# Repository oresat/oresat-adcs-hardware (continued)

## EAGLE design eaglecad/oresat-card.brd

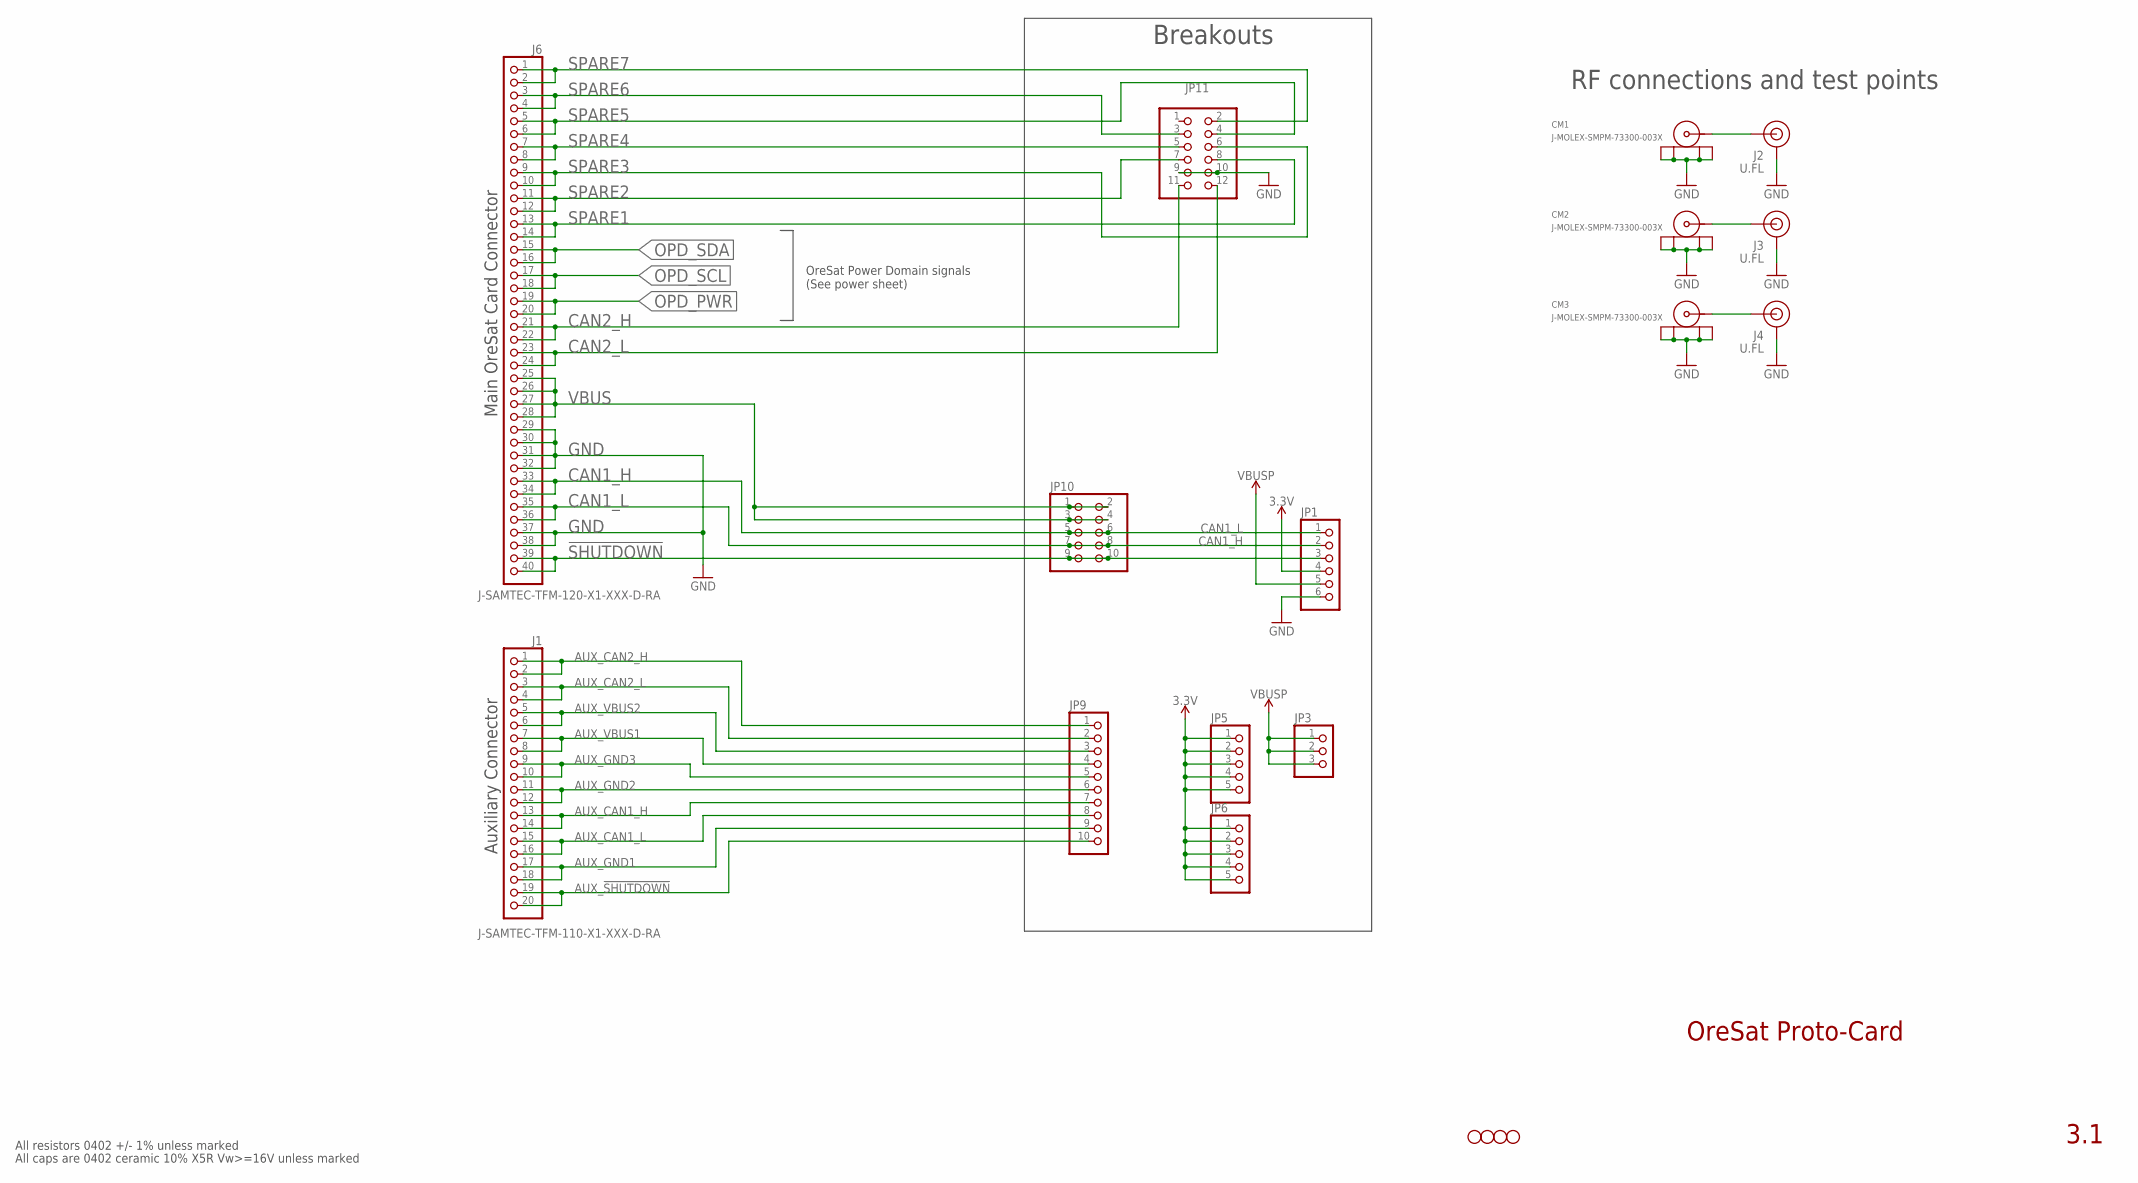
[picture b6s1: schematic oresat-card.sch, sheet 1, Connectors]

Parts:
CM1, CM2, CM3: J-MOLEX-SMPM-73300-003X; J-MOLEX-SMPM-073300-003X; MPN 73300-0020
H1, H2, H3, H4: STAND-OFFTIGHT; STAND-OFF-TIGHT
J1: J-SAMTEC-TFM-110-X1-XXX-D-RA; MPN TFM-110-01-L-D-RA
J2, J3, J4: U.FL
J6: J-SAMTEC-TFM-120-X1-XXX-D-RA; MPN TFM-120-01-L-D-RA
JP1: PINHD-1X6; 1X06
JP3: PINHD-1X3; 1X03
JP5, JP6: PINHD-1X5; 1X05
JP9: PINHD-1X10; 1X10
JP10: PINHD-2X5; 2X05
JP11: PINHD-2X6; 2X06

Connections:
3.3V: JP1.4, JP5.1, JP5.2, JP5.3, JP5.4, JP5.5, JP6.1, JP6.2, JP6.3, JP6.4, JP6.5
!SHUTDOWN: J6.39, J6.40, JP1.3, JP10.9, JP10.10
AUX_!SHUTDOWN: J1.19, J1.20, JP9.10
AUX_CAN1_H: J1.13, J1.14, JP9.7
AUX_CAN1_L: J1.15, J1.16, JP9.8
AUX_CAN2_H: J1.1, J1.2, JP9.1
AUX_CAN2_L: J1.3, J1.4, JP9.2
AUX_GND1: J1.17, J1.18, JP9.9
AUX_GND2: J1.11, J1.12, JP9.6
AUX_GND3: J1.9, J1.10, JP9.5
AUX_VBUS1: J1.7, J1.8, JP9.4
AUX_VBUS2: J1.5, J1.6, JP9.3
CAN1_H: J6.33, J6.34, JP1.1, JP10.5, JP10.6
CAN1_L: J6.35, J6.36, JP1.2, JP10.7, JP10.8
CAN2_H: J6.21, J6.22, JP11.11
CAN2_L: J6.23, J6.24, JP11.12
GND: CM1.P$1 (SHIELD3), CM1.P$2 (SHIELD2), CM1.P$3 (SHIELD1), CM1.P$4 (SHIELD), CM2.P$1 (SHIELD3), CM2.P$2 (SHIELD2), CM2.P$3 (SHIELD1), CM2.P$4 (SHIELD), CM3.P$1 (SHIELD3), CM3.P$2 (SHIELD2), CM3.P$3 (SHIELD1), CM3.P$4 (SHIELD), J2.1 (GND), J2.2 (GND), J3.1 (GND), J3.2 (GND), J4.1 (GND), J4.2 (GND), J6.29, J6.30, J6.31, J6.32, J6.37, J6.38, JP1.6, JP11.9, JP11.10; also elsewhere on the board
unnamed: CM3.RF (CENTER), J4.FEED (SIGNAL)
OPD_PWR: J6.19, J6.20; also elsewhere on the board
OPD_SCL: J6.17, J6.18; also elsewhere on the board
OPD_SDA: J6.15, J6.16; also elsewhere on the board
RF1: CM1.RF (CENTER), J2.FEED (SIGNAL)
RF2: CM2.RF (CENTER), J3.FEED (SIGNAL)
SPARE1: J6.13, J6.14, JP11.8
SPARE2: J6.11, J6.12, JP11.7
SPARE3: J6.9, J6.10, JP11.6
SPARE4: J6.7, J6.8, JP11.5
SPARE5: J6.5, J6.6, JP11.4
SPARE6: J6.3, J6.4, JP11.3
SPARE7: J6.1, J6.2, JP11.2
VBUS: J6.25, J6.26, J6.27, J6.28, JP10.1, JP10.2, JP10.3, JP10.4; also elsewhere on the board
VBUSP: JP1.5, JP3.1, JP3.2, JP3.3; also elsewhere on the board

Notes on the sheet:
OreSat Proto-Card
3.1
All resistors 0402 +/- 1% unless marked
All caps are 0402 ceramic 10% X5R Vw>=16V unless marked
Auxiliary Connector
Main OreSat Card Connector
RF connections and test points
Breakouts
OreSat Power Domain signals (See power sheet)

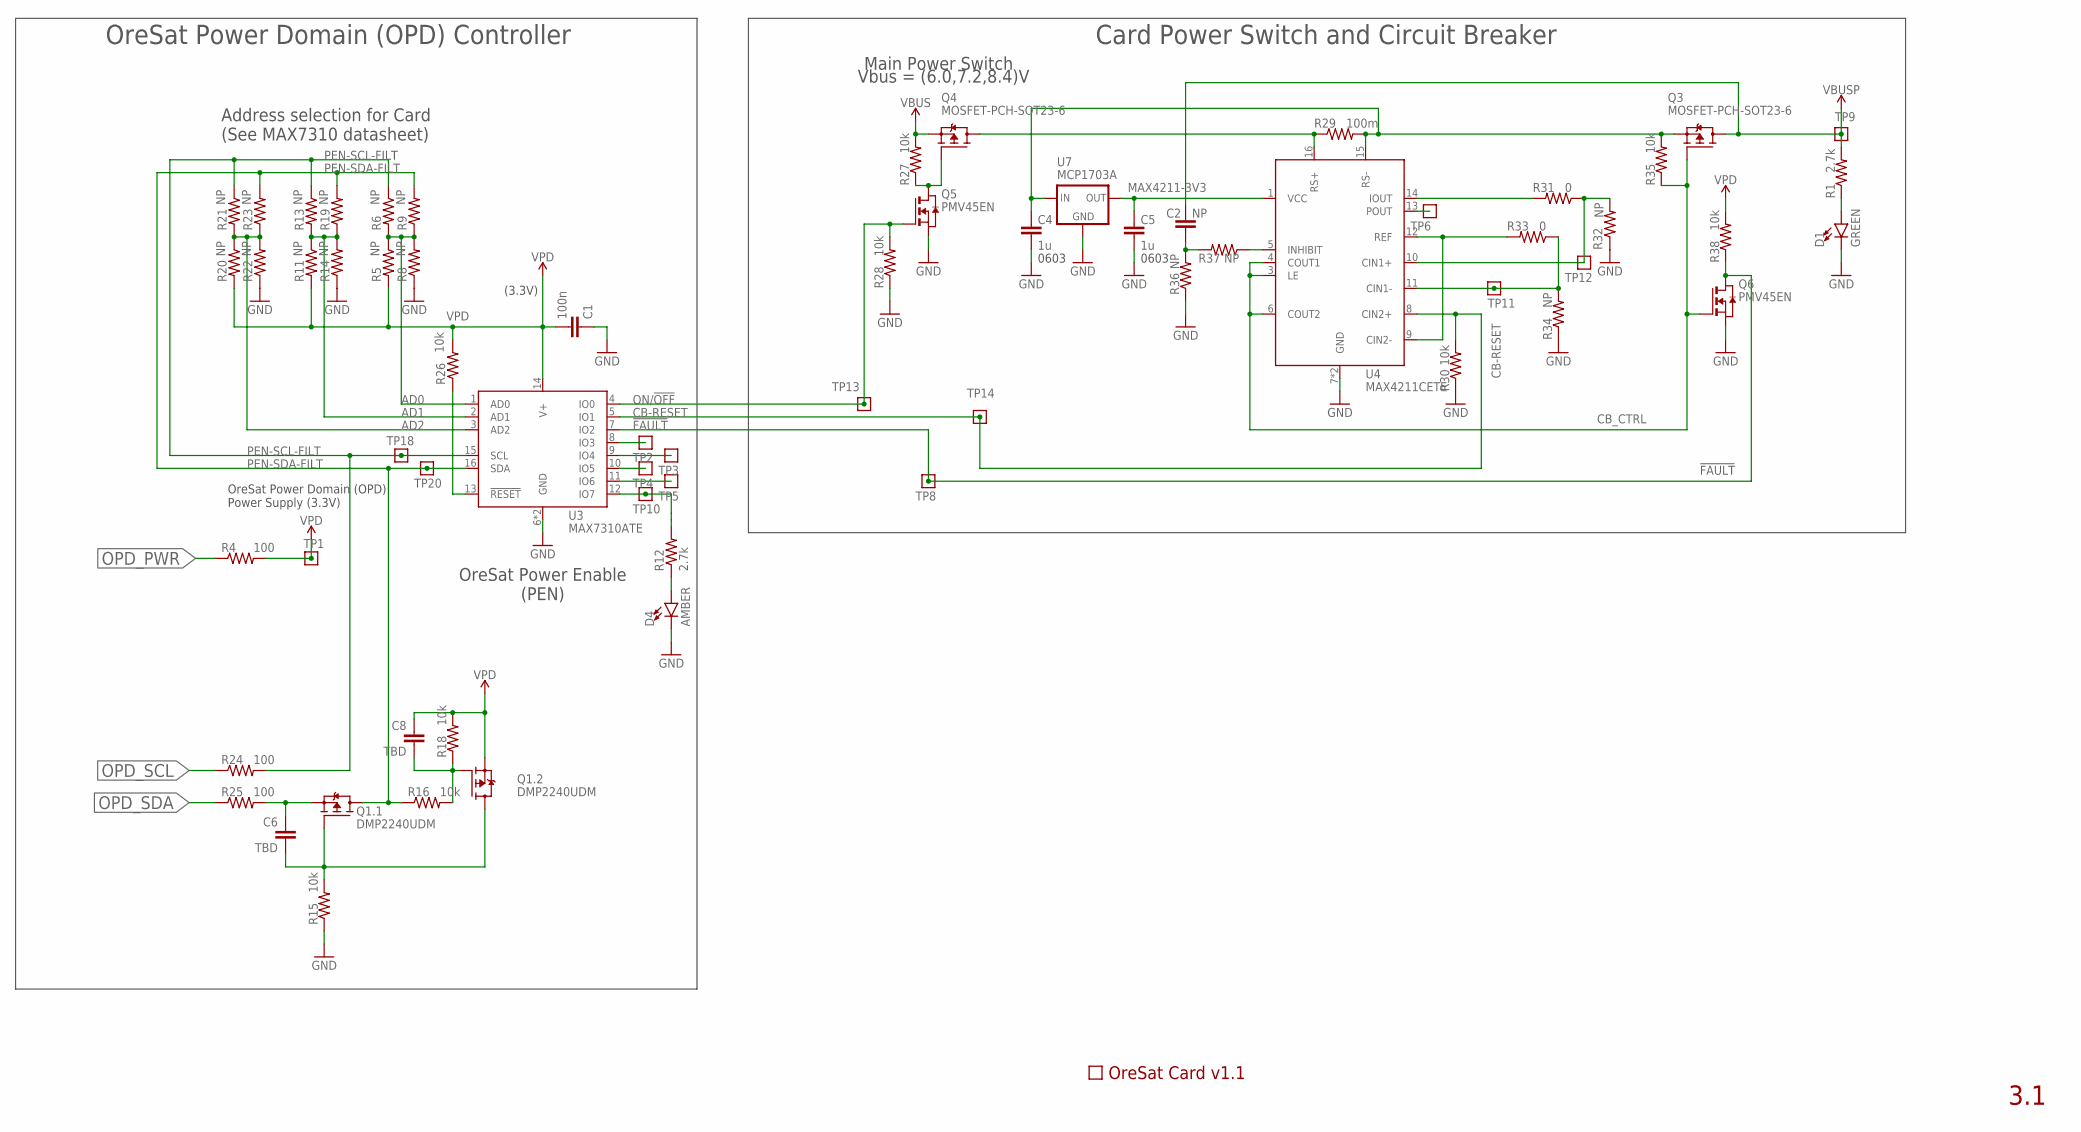
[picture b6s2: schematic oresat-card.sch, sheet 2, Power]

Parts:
C1: 100n; .0402-B-NOSILK; MPN CL05B104KO5NNNC
C2: NP; .0402-B-NOSILK; MPN CL05B104KO5NNNC
C4, C5: 1u; .0603-B-NOSILK; MPN CL05B104KO5NNNC
C6, C8: TBD; .0402-B-NOSILK; MPN CL05B104KO5NNNC
D1: GREEN; LED-0603
D4: AMBER; LED-0603
Q1: DMP2240UDM; SOT23-6; MPN DMP2240UDM
Q3, Q4: MOSFET-PCH-SOT23-6; SOT23-6; MPN DMP3050LVT-7
Q5, Q6: PMV45EN; SOT23
R1, R12: 2.7k; .0402-B-NOSILK; MPN RC1005F6653CS
R4, R24, R25: 100; .0402-B-NOSILK; MPN RC1005F6653CS
R5, R6, R8, R9, R11, R13, R14, R19, R20, R21, R22, R23, R32, R34, R36, R37: NP; .0402-B-NOSILK; MPN RC1005F6653CS
R15, R16, R18, R26, R27, R28, R30, R35, R38: 10k; .0402-B-NOSILK; MPN RC1005F6653CS
R29: 100m; R1206
R31, R33: 0; .0402-B-NOSILK; MPN RC1005F6653CS
TP1, TP2, TP3, TP4, TP5, TP6, TP8, TP9, TP10, TP11, TP12, TP13, TP14, TP18, TP20: TEST-POINT; 2MM-TEST-POINT
U3: MAX7310ATE; QFN65P400X400X80-17T210; MPN MAX7310ATE
U4: MAX4211CETE; QFN65P400X400X80-17T210; MPN MAX4211CETE
U7: MCP1703A; SOT23; MPN MCP1703AT-3302E/CB
U$1: ORESAT-CARD-V1.1-3XRF

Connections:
!FAULT: Q6.3 (D), R38.1, TP8.1, U3.7 (IO2)
AD0: R5.1, R6.2, R8.2, R9.1, U3.1 (AD0)
AD1: R11.1, R13.2, R14.2, R19.1, U3.2 (AD1)
AD2: R20.1, R21.2, R22.2, R23.1, U3.3 (AD2)
CB-RESET: R30.2, TP14.1, U3.5 (IO1), U4.8 (CIN2+)
CB_CTRL: Q3.3 (G), Q6.1 (G), R35.1, U4.3 (LE), U4.4 (COUT1), U4.6 (COUT2)
GND: C1.1, C4.2, C5.2, D1.C, D4.C, Q5.2 (S), Q6.2 (S), R8.1, R14.1, R15.1, R22.1, R28.1, R30.1, R32.1, R34.1, R36.1, U3.6 (GND), U3.EPAD (GND), U4.7 (GND), U4.EPAD (GND), U7.1 (GND); also elsewhere on the board
MAX4211-3V3: C5.1, U4.1 (VCC), U7.2 (OUT)
unnamed: D1.A, R1.1
unnamed: C4.1, Q3.4 (S), R29.2, R35.2, U4.15 (RS-), U7.3 (IN)
unnamed: TP2.1, U3.8 (IO3)
unnamed: TP3.1, U3.9 (IO4)
unnamed: TP4.1, U3.10 (IO5)
unnamed: TP5.1, U3.11 (IO6)
unnamed: R12.2, TP10.1, U3.12 (IO7)
unnamed: D4.A, R12.1
unnamed: C6.1, Q1.5 (S), R25.2
unnamed: C6.2, Q1.1 (G), Q1.4 (D), R15.2
unnamed: C8.2, Q1.3 (G), R16.2, R18.1
unnamed: R26.1, U3.13 (!RESET)
unnamed: Q4.3 (G), Q5.3 (D), R27.1
unnamed: Q4.1 (D), Q4.2 (D), Q4.5 (D), Q4.6 (D), R29.1, U4.16 (RS+)
unnamed: R31.1, R32.2, TP12.1, U4.10 (CIN1+)
unnamed: R33.1, R34.2, TP11.1, U4.11 (CIN1-)
unnamed: R31.2, U4.14 (IOUT)
unnamed: R33.2, U4.9 (CIN2-), U4.12 (REF)
unnamed: TP6.1, U4.13 (POUT)
unnamed: C2.1, R36.2, R37.2
unnamed: R37.1, U4.5 (INHIBIT)
ON/!OFF: Q5.1 (G), R28.2, TP13.1, U3.4 (IO0)
OPD_PWR: R4.1; also elsewhere on the board
OPD_SCL: R24.1; also elsewhere on the board
OPD_SDA: R25.1; also elsewhere on the board
PEN-SCL-FILT: R6.1, R13.1, R21.1, R24.2, TP18.1, U3.15 (SCL)
PEN-SDA-FILT: Q1.6 (D), R9.2, R16.1, R19.2, R23.2, TP20.1, U3.16 (SDA)
VBUS: Q4.4 (S), R27.2; also elsewhere on the board
VBUSP: C2.2, Q3.1 (D), Q3.2 (D), Q3.5 (D), Q3.6 (D), R1.2, TP9.1; also elsewhere on the board
VPD: C1.2, C8.1, Q1.2 (S), R4.2, R5.2, R11.2, R18.2, R20.2, R26.2, R38.2, TP1.1, U3.14 (V+)

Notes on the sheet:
Main Power Switch
OreSat Power Enable (PEN)
Address selection for Card (See MAX7310 datasheet)
(3.3V)
Vbus = (6.0,7.2,8.4)V
0603
OreSat Power Domain (OPD) Power Supply (3.3V)
OreSat Power Domain (OPD) Controller
Card Power Switch and Circuit Breaker
3.1

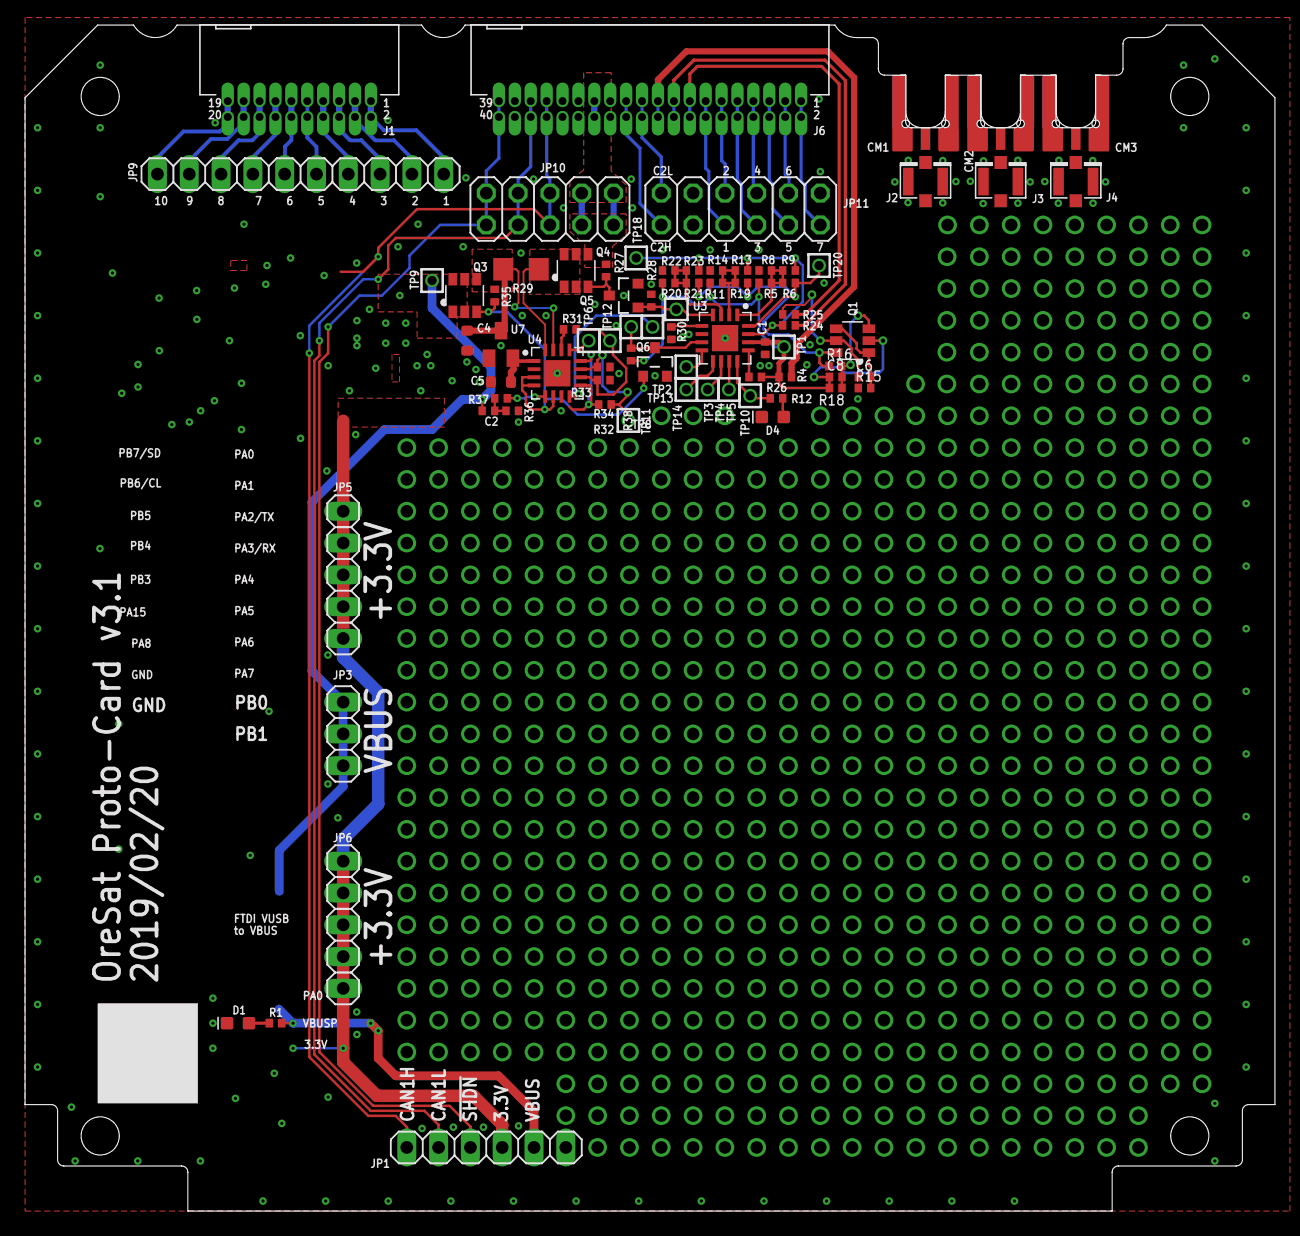
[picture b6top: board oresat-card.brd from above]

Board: 2 copper layers, 99.8 x 94.7 mm, 84 parts (0 on the bottom side), 64 nets.

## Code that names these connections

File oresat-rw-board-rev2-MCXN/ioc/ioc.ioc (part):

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Mcu.Name=STM32G474V(B-C-E)Hx
Mcu.Package=TFBGA100
Mcu.UserName=STM32G474VEHx
PA0.GPIOParameters=GPIO_Label
PA0.GPIO_Label=PHA_I
PA0.Mode=IN1-Single-Ended
PA0.Signal=ADC1_IN1
PA1.GPIOParameters=GPIO_Label
PA1.GPIO_Label=PHC_I
PA1.Mode=IN2-Single-Ended
PA1.Signal=ADC2_IN2
PA10.GPIOParameters=GPIO_Label
PA10.GPIO_Label=PHB_H
PA10.Mode=Output_TB1TB2
PA10.Signal=HRTIM1_CHB1
PA11.GPIOParameters=GPIO_Label
PA11.GPIO_Label=PHB_L
PA11.Mode=Output_TB1TB2
PA11.Signal=HRTIM1_CHB2
PA13.Mode=Trace_Synchro_4bits_SW
PA13.Signal=SYS_JTMS-SWDIO
PA14.Mode=Trace_Synchro_4bits_SW
PA14.Signal=SYS_JTCK-SWCLK
PA15.GPIOParameters=GPIO_Label
PA15.GPIO_Label=SPI_nCS
PA15.Mode=NSS_Signal_Hard_Output
PA15.Signal=SPI3_NSS
PA2.GPIOParameters=GPIO_Label
PA2.GPIO_Label=PHA_V
PA2.Mode=IN3-Single-Ended
PA2.Signal=ADC1_IN3
PA4.GPIOParameters=GPIO_Label
PA4.GPIO_Label=DAC_1
PA4.Signal=COMP_DAC11_group
PA5.GPIOParameters=GPIO_Label
PA5.GPIO_Label=DAC_2
PA5.Signal=COMP_DAC12_group
PA6.Signal=COMP_DAC21_group
PA7.GPIOParameters=GPIO_Label
PA7.GPIO_Label=PHC_V
PA7.Mode=IN4-Single-Ended
PA7.Signal=ADC2_IN4
PA8.GPIOParameters=GPIO_Label
PA8.GPIO_Label=PHA_H
PA8.Mode=Output_TA1TA2
PA8.Signal=HRTIM1_CHA1
PA9.GPIOParameters=GPIO_Label
PA9.GPIO_Label=PHA_L
PA9.Mode=Output_TA1TA2
PA9.Signal=HRTIM1_CHA2
PB1.GPIOParameters=GPIO_Label
PB1.GPIO_Label=PHB_I
PB1.Mode=IN1-Single-Ended
PB1.Signal=ADC3_IN1
PB3.GPIOParameters=GPIO_Label
PB3.GPIO_Label=SWO
PB3.Signal=GPIO_Output
PB5.GPIOParameters=GPIO_Label
PB5.GPIO_Label=CAN_ADDR1
PB5.Signal=GPIO_Input
PB7.GPIOParameters=GPIO_Label
PB7.GPIO_Label=CAN_ADDR0
PB7.Signal=GPIO_Input
PB8-BOOT0.GPIOParameters=GPIO_Label
PB8-BOOT0.GPIO_Label=BOOT0
PB8-BOOT0.Signal=GPIO_Input
PC10.GPIOParameters=GPIO_Label
PC10.GPIO_Label=SPI_SCK
PC10.Mode=Full_Duplex_Master
PC10.Signal=SPI3_SCK
PC11.GPIOParameters=GPIO_Label
PC11.GPIO_Label=SPI_MISO
PC11.Mode=Full_Duplex_Master
PC11.Signal=SPI3_MISO
PC12.GPIOParameters=GPIO_Label
PC12.GPIO_Label=SPI_MOSI
PC12.Mode=Full_Duplex_Master
PC12.Signal=SPI3_MOSI
PC8.GPIOParameters=GPIO_Label
PC8.GPIO_Label=PHC_H
PC8.Mode=Output_TE1TE2
PC8.Signal=HRTIM1_CHE1
PC9.GPIOParameters=GPIO_Label
PC9.GPIO_Label=PHC_L
PC9.Mode=Output_TE1TE2
PC9.Signal=HRTIM1_CHE2
PD0.GPIOParameters=GPIO_Label
PD0.GPIO_Label=CAN_RX
PD0.Mode=FDCAN_Activate
PD0.Signal=FDCAN1_RX
PD1.GPIOParameters=GPIO_Label
PD1.GPIO_Label=CAN_TX
PD1.Mode=FDCAN_Activate
PD1.Signal=FDCAN1_TX
PD2.GPIOParameters=GPIO_Label
PD2.GPIO_Label=DEBUG1
PD2.Signal=GPIO_Output
PD3.GPIOParameters=GPIO_Label
PD3.GPIO_Label=DEBUG3
PD3.Signal=GPIO_Output
PD4.GPIOParameters=GPIO_Label
PD4.GPIO_Label=DEBUG0
PD4.Signal=GPIO_Output
PD5.GPIOParameters=GPIO_Label
PD5.GPIO_Label=DEBUG_TX
PD5.Mode=Asynchronous
PD5.Signal=USART2_TX
PD6.GPIOParameters=GPIO_Label
PD6.GPIO_Label=DEBUG_RX
PD6.Mode=Asynchronous
PD6.Signal=USART2_RX
PD7.GPIOParameters=GPIO_Label
PD7.GPIO_Label=DEBUG2
PD7.Signal=GPIO_Output
PE0.GPIOParameters=GPIO_Label
PE0.GPIO_Label=DFU_TX
PE0.Mode=Asynchronous
PE0.Signal=USART1_TX
PE1.GPIOParameters=GPIO_Label
PE1.GPIO_Label=DFU_RX
PE1.Mode=Asynchronous
PE1.Signal=USART1_RX
PE10.GPIOParameters=GPIO_Label
PE10.GPIO_Label=THERM3
PE10.Mode=IN14-Single-Ended
PE10.Signal=ADC5_IN14
PE11.GPIOParameters=GPIO_Label
PE11.GPIO_Label=THERM2
PE11.Mode=IN15-Single-Ended
PE11.Signal=ADC5_IN15
PE12.GPIOParameters=GPIO_Label
PE12.GPIO_Label=THERM0
PE12.Mode=IN16-Single-Ended
PE12.Signal=ADC5_IN16
PE14.GPIOParameters=GPIO_Label
PE14.GPIO_Label=VBUS_V
PE14.Mode=IN1-Single-Ended
PE14.Signal=ADC4_IN1
PE2.Mode=Trace_Synchro_4bits_SW
PE2.Signal=SYS_TRACECLK
PE3.Mode=Trace_Synchro_4bits_SW
PE3.Signal=SYS_TRACED0
PE4.Mode=Trace_Synchro_4bits_SW
PE4.Signal=SYS_TRACED1
PE5.Mode=Trace_Synchro_4bits_SW
PE5.Signal=SYS_TRACED2
PE6.Mode=Trace_Synchro_4bits_SW
PE6.Signal=SYS_TRACED3
PE8.GPIOParameters=GPIO_Label
PE8.GPIO_Label=THERM1
PE8.Mode=IN6-Single-Ended
PE8.Signal=ADC5_IN6
PE9.GPIOParameters=GPIO_Label
PE9.GPIO_Label=PHB_V
PE9.Mode=IN2-Single-Ended
PE9.Signal=ADC3_IN2
PF0-OSC_IN.Mode=HSE-External-Oscillator
PF0-OSC_IN.Signal=RCC_OSC_IN
PF1-OSC_OUT.Mode=HSE-External-Oscillator
PF1-OSC_OUT.Signal=RCC_OSC_OUT
PG10-NRST.GPIOParameters=GPIO_Label
PG10-NRST.GPIO_Label=nRST
PG10-NRST.Signal=GPIO_Input
RCC.HSE_VALUE=8000000
RCC.SYSCLKFreq_VALUE=144000000
RCC.SYSCLKSource=RCC_SYSCLKSOURCE_PLLCLK
board=custom

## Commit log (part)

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2018-02-22 Cosmetic fixes: Added labels. All resistors and capacitors are numbered. Updated the symbol of the encoder. Updated the symbol and package of the STSPIN230. Boxed LEDs and placed a note "NP FOR FLIGH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
2018-02-23 Added a testpoint to the CAN transciever.
2018-02-24 Nice job, Nathan! Did a bit of visual polish, updated AMS symbol to be more compact. Big changes: Added new TPS63070 SPS circuit from solar board, redid LEDs on magnetorquer. BLDC LEDs should be that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
2018-02-24 Checked all ERC. Looks good. Eric go ahead and start board layout again.
2018-02-26 Resized component packages for power considerations and for package size consistency.
2018-02-26 Layout Start
    Start organization of board layout
2018-03-02 finished power/started BLDC d
2018-03-02 add Q-out/ more on layout
    Quadrature output has been added to the schematic for Josh to collect data from motor spec test.
2018-03-04 Nealy dere
2018-03-06 Board Rev1
2018-03-10 Here's what I have for the BOM.
2018-03-13 Board to send out
2018-03-19 First revision of a hardware guide which describes all the hardware components in the motor controller schematic. There are a couple of components I wasn't sure about. This document needs a little mo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
2018-03-30 Schematic PDFs
2018-03-30 Updated PDF
2018-04-27 [WIP] restore from workstation @E-Ruhl
2018-05-11 rev2 LFD
2018-05-12 part placement on rev3
2018-05-13 rev 3 progress
2018-05-15 rev3 needs design review
2018-05-15 Rev 3 Ready for final sendout (Don't forget the stencils)
2018-05-15 last change, I'm pretty sure
2018-05-21 Clean up from last week: added three test points because test points are important when you might need a signal, and added signal names because N names are dumb, and cleaned up a few ERC warnings. An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
2018-05-22 Manufacturing photos looks like OSHpark boards. These photos are good for documentation and presentation.
2018-05-22 Schematic photos for documentation
2018-05-23 rev2
2018-05-24 poster picture
2018-05-24 poster print
    touched up pad overlap
2018-06-05 Images of schematic files for both Rev1.1 and Rev3.
2018-06-05 Created a PDF of Rev 3 schematic.
2018-06-15 For some reason the previous PDF only had page 1. I fixed it now.
2018-06-16 Formatting the readme with block diagram photos.
2018-06-16 Adding block diagram to readme
2018-06-16 Adding level 2 block diagram to readme
2018-06-16 Adding info on block diagram systems.
2018-06-16 Made a project requirements document as markdown.
2018-06-16 Fixed some formatting mistakes.
2018-06-16 Changed name to make more sense.
2018-06-16 Fixed table formatting.
2018-06-17 Added schematic photos to readme
2018-06-17 I'm bad at formatting...
2018-06-17 *sign* I have to push every few changes to make sure I'm doing this correctly...
2018-06-17 Adding the capstone poster to the readme file.
2018-06-17 Changed the hardware reference guide from a word file to a markdown file.
2018-06-17 Added research references in markdown format.
2018-06-17 Added Research references and bibliography.md
2018-06-17 deleting PDF folder
2018-06-18 Updated readme and added SOP for board stuffing.
2018-06-18 comp
2018-06-18 Adding readme file and new folder
    folder ACS Capstone
2018-06-18 Update Readme.md
    Testing to see if images show after changes.
2018-06-18 Update Readme.md
    Adding schematic photos
2018-06-18 Update Readme.md
    Adding the rest of the pictures
2018-06-18 Add photos
2018-06-18 Update Ramp Up
2018-06-18 adding important files
2018-06-18 adding correct system diagram
2018-06-18 system diagram png
2019-03-04 f4 updates
2019-06-25 L4 updates
2019-06-28 Prelim final rev completed + design overhaul
2019-06-29 archived
2019-06-30 Post review updates
2019-07-10 reorganization
2019-07-10 schematic updates for Hardware reference guide
2019-07-10 Hardware updates
2019-07-11 start of 4.1 and OreSat card
2019-07-16 Current set of modifications for Rev4.1 completed, some errors found and corrected
2019-07-16 Board images
2019-07-19 mods
2019-07-24 order update
2019-08-14 Placing extra circuit breakers for ACS card
2019-08-19 Oresat Card
2019-08-21 ACS card updates
2019-08-24 L4 pinout update
2019-08-31 Adding grant proposal and final report PDFs
    from OreSat Shared Drive
2019-09-07 Board connector update
2019-09-08 rev4.2 ready for review
2019-09-20 added quadrent marker resistors and tappered lower corners for more clearence
2019-09-24 layer 2 mod
2020-01-07 updated design block for card power system
2020-01-08 power domain updates
2020-01-14 ACS oresat standard card adapted for group routing
2020-01-27 Flex cable prototype
2020-01-27 file organizing
2020-01-27 mechanical outlines
2020-01-27 Final polish on v4.2b; sent off to OSH Park.
2020-01-29 Sanity check Eric's card. Removing supply symbols even though this is causing Andrew physical pain but EAGLE can't deal with renaming supply symbols. Also more text.
2020-06-26 Layed out power domains for four quadrants, added another power domain and an STM32F042. Also added breaker circuit and I2C buffer for Magnetometers, and an IMU
2020-06-30 Flattening rev4.3
2020-07-02 Reworked board layout to avoid space taken up by inhibit switches on battery board
2020-07-15 Cleaned up bNames layer, and added ground vias around board
2020-07-20 Floated BMI088 CSB2 because CSB1 was and data sheet said it had a pull up; switched to card outline with no RF connectors (whoops), moved ground stitching near edges to under TSTOP, fixed some DRC er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
2020-07-25 Added first version of acs card bom
2020-07-27 Flattening the board
2020-07-31 traces routed, still needs polygons and planes
2020-08-06 Board Flattened ready for review
2020-08-07 test point update for rev 4.3
2020-08-11 flat board ready for second round of inspection
2020-09-08 Doubled up MAG_SDA and MAG_SCL on backplane connector to match backplane, and added pull up resistors for these signals. Updated BOM to reflect this.
2020-09-21 Standardized passives to 0603 and changed all test points to circular footprint. Spaced out components in OPD for easier stuffing. Cleaned up names layer. Fixed OPD protection circuit to match OPD de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
2020-09-22 Fixed attributes and updated BOM. Also doubled up backplane connector lines and added some test points.
2020-09-23 Added flight marker
2020-09-23 Updated flight marker
2021-04-07 Create .~lock.oresat-acs-card-bom.xlsx#
2022-01-20 Rev 5.0
2022-02-07 Rev 6 pre design review
2022-02-07 Fixed ERC/DRC errors and design rules
2022-02-08 Fix DRC issues on power stage
2022-02-09 Added BoM, fixed footprints
2022-02-09 Remove temp file
2022-02-10 Added production files for ground split version
2022-02-10 Add nonsplit ground version
2022-04-03 Rev 7 power stage schematic complete
2022-04-04 Prelim power stage layout
2022-04-05 Add 3dmodels for TSON FET
2022-04-06 Design review changes
2022-05-10 Pushing changes to rev7
2022-06-30 Updated PCB layoud. Changed magnetorquer connection to 6 position pin terminal
2022-07-12 Updated 5V regulators to match design block. Added UART switch to microcontroller. Added power flags and cleaned up ERC errors
2022-07-19 Updated some attributes and resistor values to clean up BOM
2022-07-19 Beginning cleanup of the ADCS repo. Removing kicad and eaglecad and trying to make sense of all of this.
2022-07-19 Moved ACS card BOM into ACS card folder.
2022-07-19 Moved old documentation into archive and deleted some really really old stuff. Created a documentation folder.
2022-07-21 Updated card name. Now oresat-adcs-card instead of oresat-acs-card.
2022-07-22 Update README.md
    Better formatting, bring license up
2022-07-24 Updated inductor footprint
2022-08-18 Added ADCS card block diagram v1.0
2022-09-29 Updating
2022-10-07 Legacy rev6
2022-10-07 please do not touch my directory structure until this is in space
2022-10-12 Switch to running mag encoder on 3v3, move to OResat standard debug connector
2022-11-20 Added breakout board for RW mezzanine connector
2023-01-15 Extended mezzanine flex pcb so that we can slide the connector, and added silkscreen name
2023-02-13 Fixed ADCS card issues
2023-02-20 Fixed more ADCS card issues
2023-05-17 Quick commit pre-board changes
2023-05-28 Add v7.1
2023-06-07 Responding to review notes
2023-06-07 Fix clearances, fix silk, add vias
2023-06-12 Cleanup stitching on power stage, cleanup DRC control stage, add AS5047P breakout for wheel testingf
2023-07-20 Updated ADCS card and fixed library issues
2023-11-05 Push power stage rev 7.2 - production
2023-11-13 Updated date on silkscreen
2023-11-22 Changed sensor-power schematic filename to card-power
2023-11-27 Put build products (gerbers) in the build directory, and ignore archive and build directories in git.
2023-12-04 Remove old stencil files
2023-12-04 Unbreak symbol/fp libs
2024-02-25 changed mezanine flex board to shorten to 14.5mm down from 19mm
2024-02-26 CAM settings in PCB file.
2024-05-03 Remove some build files.
2024-05-03 Upgrade to KiCAD 8!
2024-05-19 Fixed missing component values
2025-09-28 New project directories for splitting up adcs card schematics
2025-11-09 Magnetorquer ADCS Board
    Magnetorquer and reaction wheel breakout; changed schematic to use hierarchy style labels instead of global net labels. Changed uC to MCXN from STM32. Changed backplane connector to OreSat 1 connecto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
2025-11-11 MCXN RW Control Board Revision 4
2025-11-23 Finished Schematic
    Added MCXN uC, new ICM-42688-P IMU, removed reaction wheels, reannotated schematics, etc.
2025-11-23 Removed temporary file
2025-11-24 Updated schematic symbols
    Updated schematic symbols to have yellow background and fixed a couple of local net labels
2025-12-15 Housekeeping items before board layout
    Changed capacitor to C_Small, changed transistor schematic symbols, moved C5 down to iC, changed 10k pull ups to 4.7k pull ups onto root page. Changed U10 and U9 so that they have the yellow backgrou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
2025-12-16 Schematic Update
    Updated schematic to fix all ERC violations and errors, removed all traces of old EAGLE imported components and replaced with either OreSat or Kicad native symbols and footprints.
2025-12-17 Updated schematic pin names and directions.
2025-12-19 Design review changes on schematic.
    Fixed UART lines, relabeled some OPD outputs from the MAX7310, fixed I2C pullups, lots of small polishing. Ready for layout.
2025-12-28 Pushed because Andrew told me to
2025-12-28 Rename to oresat-rw-card, which is what this is.
2026-01-01 RW card needs scrutiny
2026-01-07 Schematic Done + Board outline set
    Fixed heirarchical labels, cleaned up ERCs, board is ready for layout
2026-02-09 Push for design review
2026-02-20 Push for critiques
2026-02-22 Found a layout that works, barely, needs lots of cleanup!
2026-02-27 rough layout finished
2026-03-01 Mag card- Finished
    Completed PCB layout and routing.
2026-03-04 Commit because I was told to
    Also fixed a lot of things
2026-03-08 main connector done
2026-03-09 Silkscreen cleaned up
2026-03-09 Schematic and layout polishing and prep for fabrication
    Updated schematic symbols, cleaned up schematic pages to be more like protocard, removed uncessessary TPs, updated layout, cleaned up layout routing and some zones, added Makefile and READMEs for fab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
2026-03-10 Fixed a few small BOM issues, checked everything, ready for fab.
2026-03-12 Update
    Updated footprints, symbols, and pcb layout to have IMU in center of board.
2026-03-29 Final touch ups
    Added new j3 connector, and final touch ups
2026-03-30 Update before fab!
    Last final changes to pcb before fab: changed location of connector back to original. Changed silk screen to reflect date and mag board v1.0
2026-04-02 Sent off for fabrication.
    Last sweep of BOM, ground stitching, and inner layer planes. Lots of small tweaks.
2026-04-03 Fixed Footprint/Symbol Library Issue
2026-04-03 Formatted for *make* to work
2026-04-06 Fix BOM - some packages were wrong size, caught by CM.
2026-04-07 Final mag card
    Lots of polishing around best practices layout. Put in giant hole to thread the MTs from below if required for the 3U CubeSats. Cleaned up power layer, added stitching vias, updated readme.
2026-04-07 Remove old back side silkscreen
2026-04-08 Updated BOM part
2026-04-20 Updated keepout on MCXN RW board mezzanine connector and fixed kicad .gitignore for kicad 10
2026-04-20 RW Flex board for Mezzanine connectors v1.2
    This board is for RW board v8.0 and RW card v1.0. Note specialized Makefile for flex board including stiffeners.
2026-04-21 Updated Version on Board & Schematic
2026-05-07 Updated VSNS Resistor Values to Properly Reflect 3.0V ADC Reference
